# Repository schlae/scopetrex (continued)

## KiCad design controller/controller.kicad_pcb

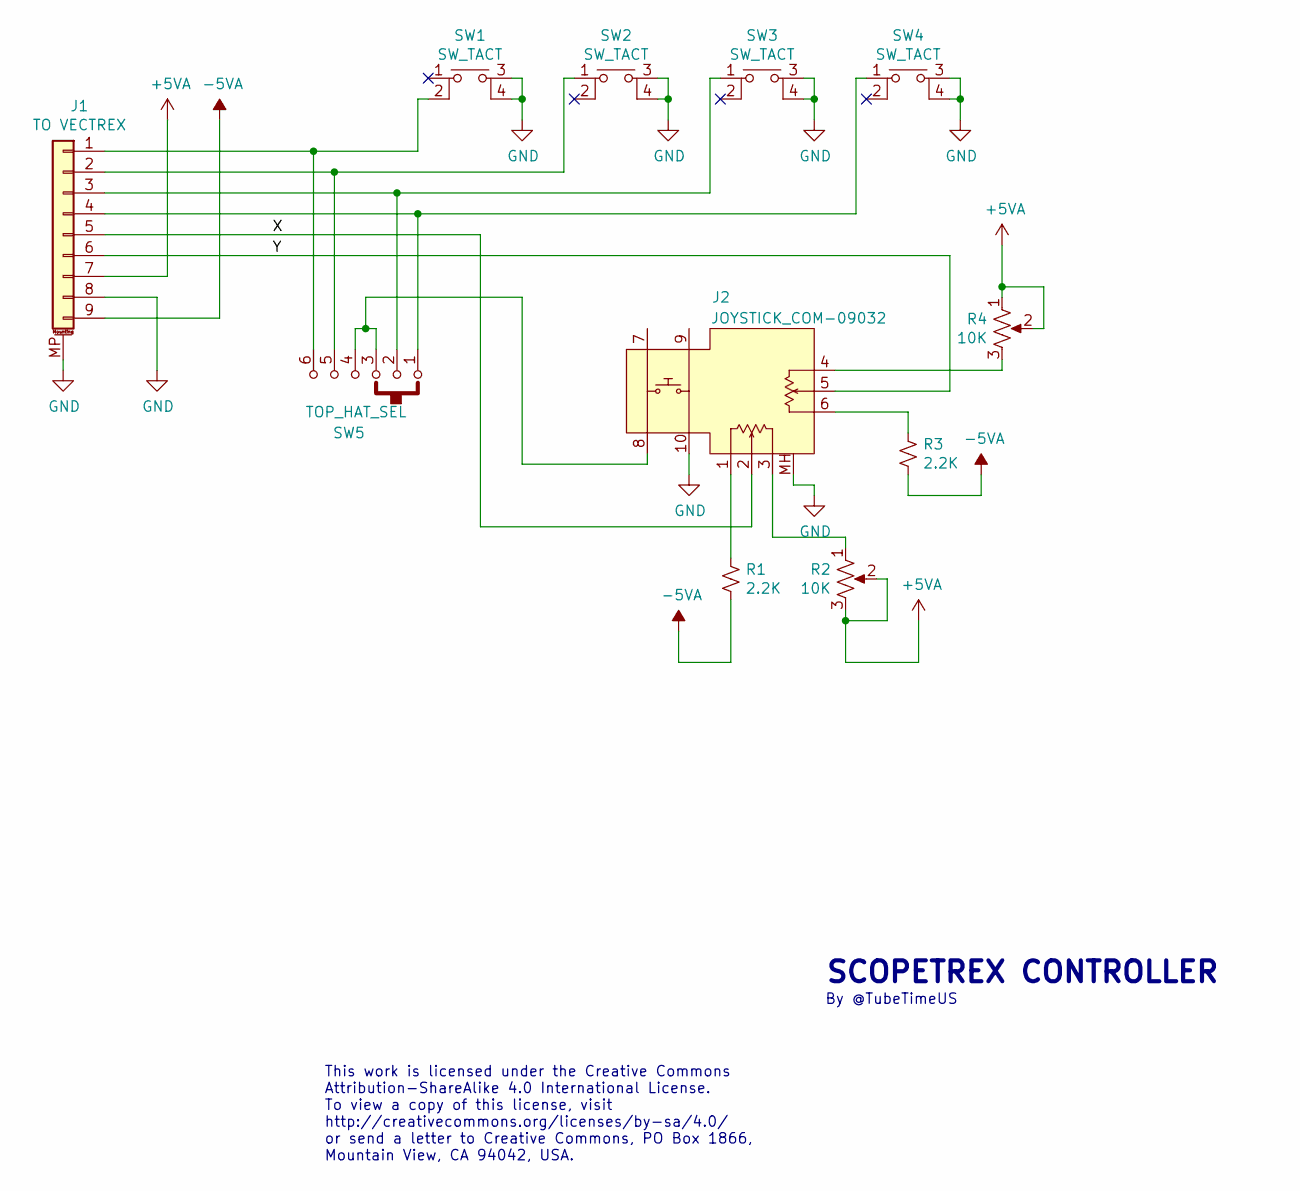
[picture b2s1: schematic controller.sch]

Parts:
J1: TO VECTREX; DB9FC2; Mouser 806-K22X-E9S-NR
J2: JOYSTICK_COM-09032; Digikey 1568-1526-ND
R1, R3: 2.2K; RESA500; Mouser 603-CFR-25JR-522K2
R2, R4: 10K; PIHER_PT10_V10; Mouser 531-PT10LV113A22PMS
SW1, SW2, SW3, SW4: SW_TACT; ALPS_SKHC; Mouser 688-SKHCBKA010
SW5: TOP_HAT_SEL; CK_SK-14D01-G-6; Mouser 611-SK-14D01-G6

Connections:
+5VA: J1.7, R2.2, R2.3, R4.1, R4.2
-5VA: J1.9, R1.2, R3.2
/X: J1.5, J2.2 (X2)
/Y: J1.6, J2.5 (Y2)
GND: J1.8, J1.MP (MountPin), J2.10 (SW2B), J2.MH, SW1.3, SW1.4, SW2.3, SW2.4, SW3.3, SW3.4, SW4.3, SW4.4, SW5.7 (GND)
unnamed: J1.1, SW1.2, SW5.6
unnamed: J1.2, SW2.1, SW5.5
unnamed: J1.3, SW3.1, SW5.2
unnamed: J1.4, SW4.1, SW5.1
unnamed: J2.1 (X1), R1.1
unnamed: J2.3 (X3), R2.1
unnamed: J2.4 (Y1), R4.3
unnamed: J2.6 (Y3), R3.1
unnamed: J2.8 (SW1B), SW5.3, SW5.4

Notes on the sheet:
This work is licensed under the Creative Commons Attribution-ShareAlike 4.0 International License. To view a copy of this license, visit http://creativecommons.org/licenses/by-sa/4.0/ or send a letter to Creative Commons, PO Box 1866, Mountain View, CA 94042, USA.
SCOPETREX CONTROLLER
By @TubeTimeUS

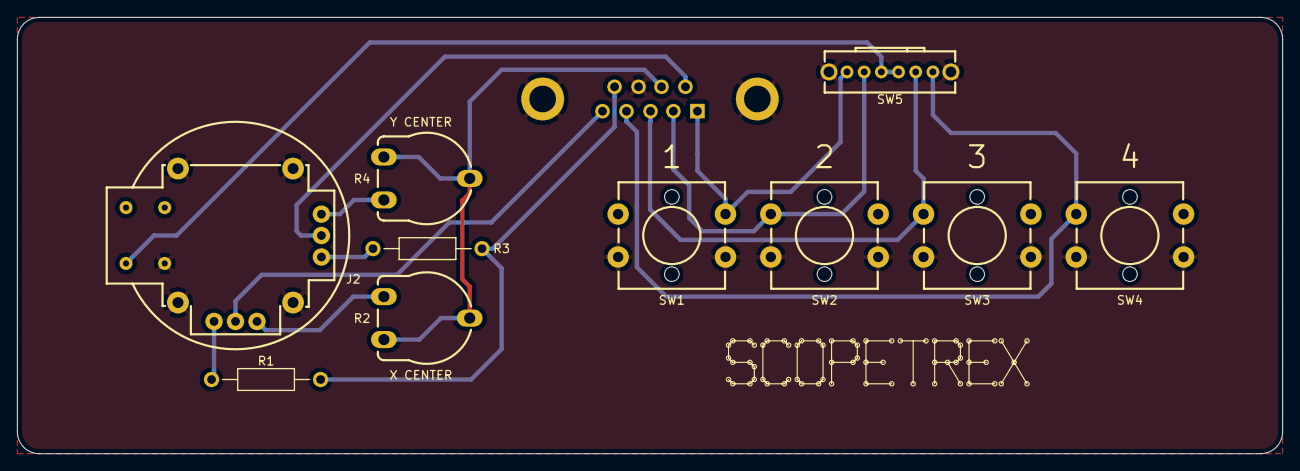
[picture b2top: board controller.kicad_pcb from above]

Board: 2 copper layers, 147.3 x 50.8 mm, 11 parts (1 on the bottom side), 14 nets.

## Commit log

2020-05-07 Commit of rev 1.1 files
2020-05-07 Add schematic
2020-05-07 Formatting in README
2020-05-08 better part for right angle cart slot
2020-05-10 Fix FB201 value and change C238 to 22uF
2020-05-10 Add missing mouser reference
    This adds the joystick to the mouser BOM
2022-10-06 Correct Mouser part number for R103. Was 2K, should be 22K.
2024-08-21 Fix interrupt line issue
